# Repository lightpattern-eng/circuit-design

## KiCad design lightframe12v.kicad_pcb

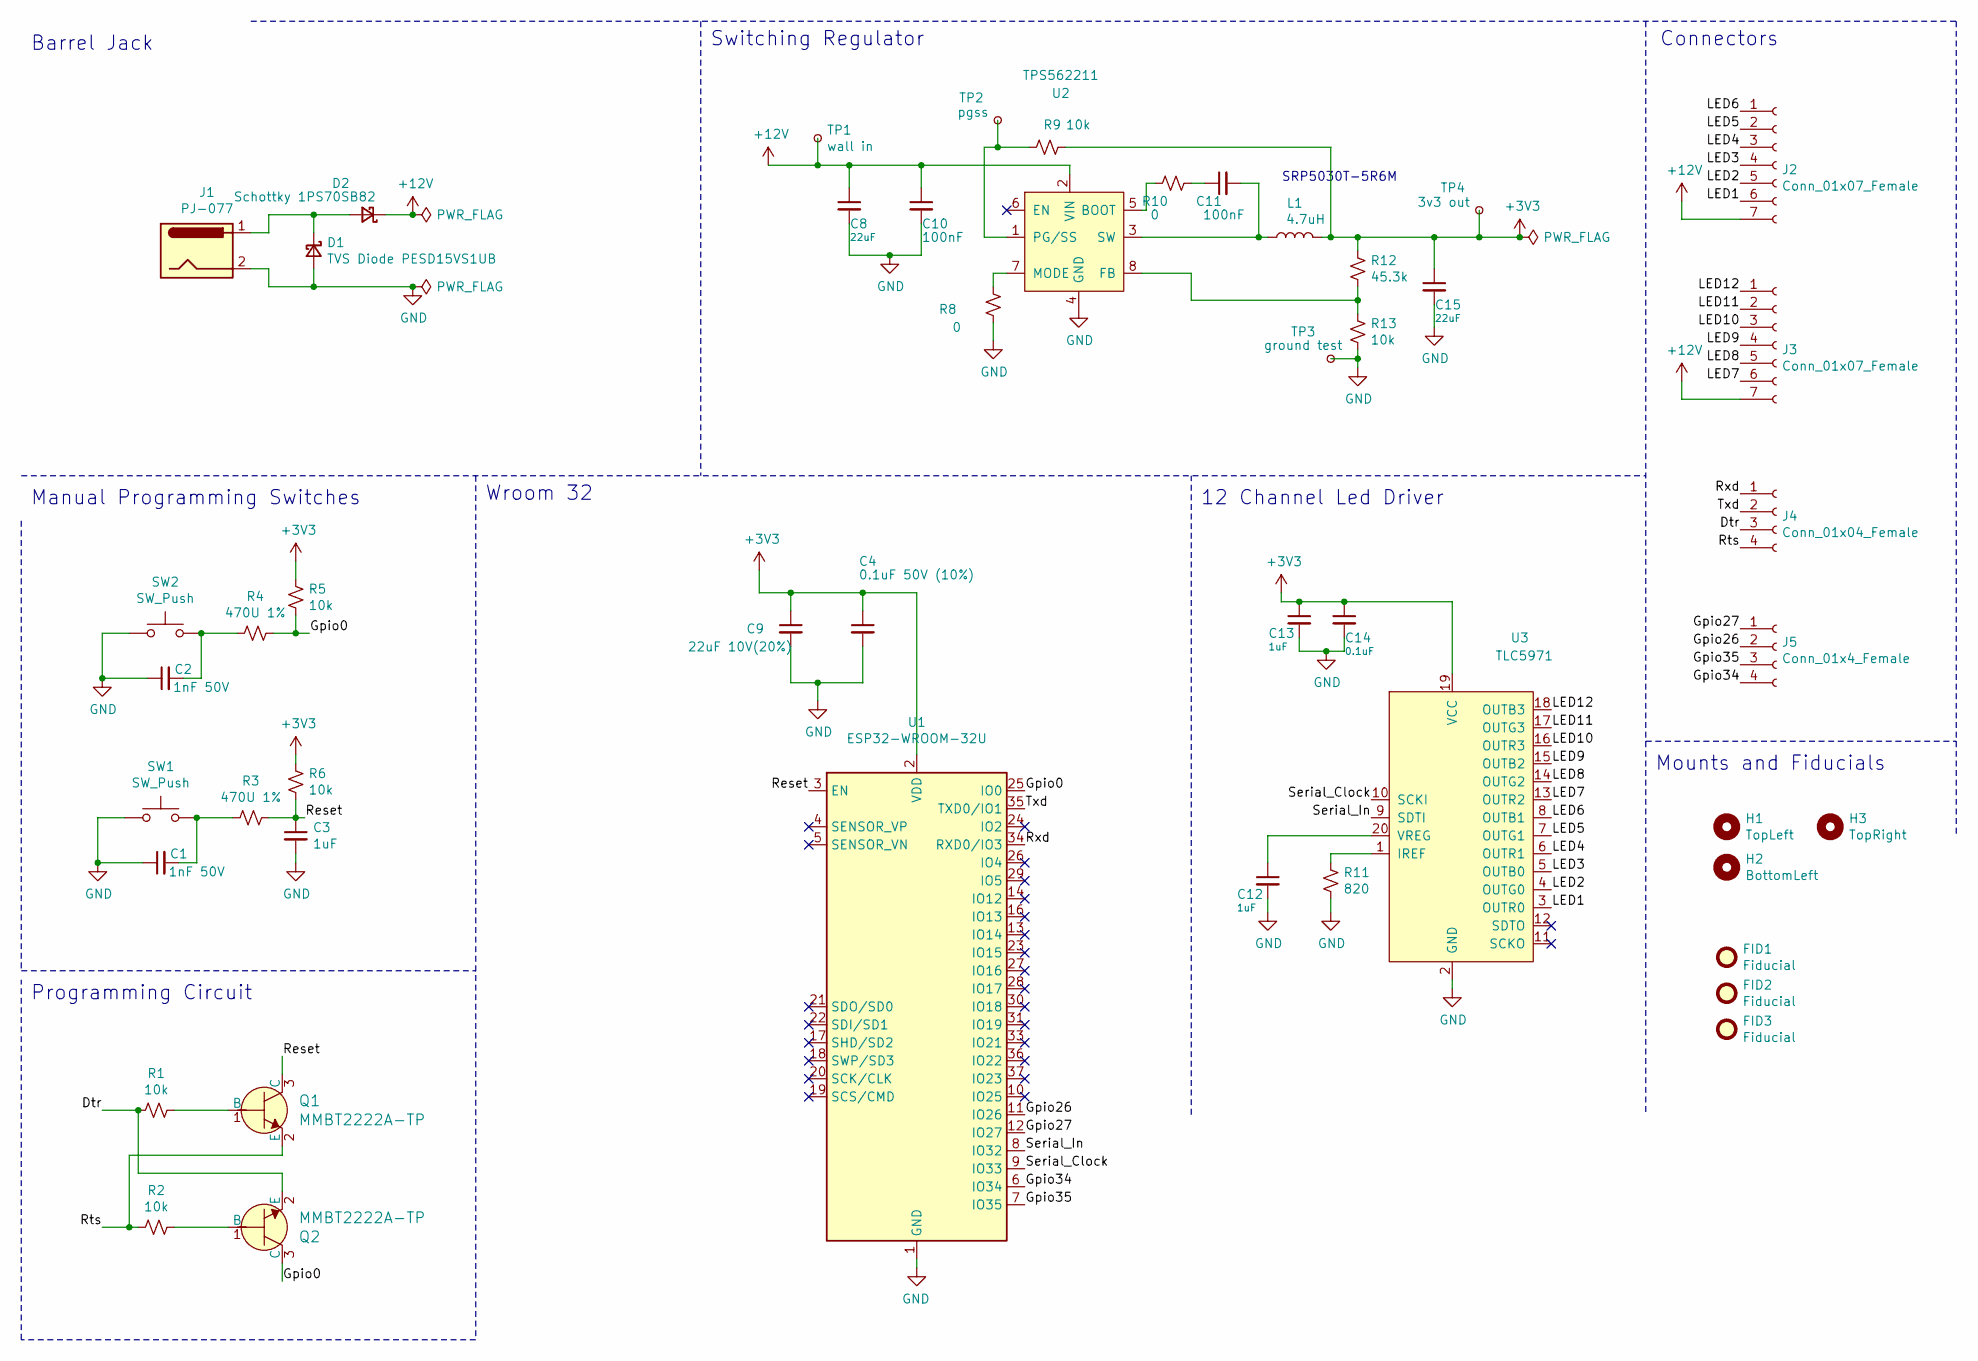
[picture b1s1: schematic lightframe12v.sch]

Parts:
C1, C2: 1nF 50V; 0603
C3, C12, C13: 1uF; 0603
C4: 0.1uF 50V (10%); 0603
C8: 22uF; 1206
C9: 22uF 10V(20%); 0805
C10: 100nF; 0603
C11: 100nF; 0805
C14: 0.1uF; 0603
C15: 22uF; 0805
D1: TVS Diode PESD15VS1UB; D_SOD-523
D2: Schottky 1PS70SB82; SOT-323
FID1, FID2, FID3: Fiducial; Fiducial_1mm_Mask2mm
H1: TopLeft; MountingHole_2.2mm_M2
H2: BottomLeft; MountingHole_2.2mm_M2
H3: TopRight; MountingHole_2.2mm_M2
J1: PJ-077; CUI_PJ-077
J2, J3: Conn_01x07_Female; PinHeader_1x07_P2.54mm_Vertical
J4: Conn_01x04_Female; PinSocket_1x04_P2.54mm_Vertical
J5: Conn_01x4_Female; PinHeader_1x04_P2.54mm_Vertical
L1: 4.7uH; SRP5030T-5R6M
Q1, Q2: MMBT2222A-TP; SOT-23-3; MPN MMBT2222A-TP; Digi-Key_PN MMBT2222ATPMSCT-ND
R1, R2, R5, R6: 10k; R_0402_1005Metric
R3, R4: 470U 1%; 0603
R8, R10: 0; 0603
R9, R13: 10k; 0603
R11: 820; 0603
R12: 45.3k; 0603
SW1, SW2: SW_Push; PTS810 Tactile Switch
TP1: wall in; TestPoint_Pad_1.5x1.5mm
TP2: pgss; TestPoint_Pad_1.5x1.5mm
TP3: ground test; TestPoint_Pad_1.5x1.5mm
TP4: 3v3 out; TestPoint_Pad_1.5x1.5mm
U1: ESP32-WROOM-32U
U2: TPS562211; TPS562211 12V pmic
U3: TLC5971; HTSSOP-20-1EP_4.4x6.5mm_P0.65mm_EP3.4x6.5mm_Mask2.75x3.43mm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

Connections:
+3V3: C4.1, C9.1, C13.1, C14.1, C15.1, L1.2, R5.1, R6.1, R9.1, R12.1, TP4.1, U1.2 (VDD), U3.19 (VCC)
+12V: C8.1, C10.1, D2.1 (K), J2.7, J3.7, TP1.1, U2.2 (VIN)
/Dtr: J4.3, Q2.2 (E), R1.2
/Gpio0: Q2.3 (C), R4.2, R5.2, U1.25 (IO0)
/Gpio26: J5.2, U1.11 (IO26)
/Gpio27: J5.1, U1.12 (IO27)
/Gpio34: J5.4, U1.6 (IO34)
/Gpio35: J5.3, U1.7 (IO35)
/LED1: J2.6, U3.3 (OUTR0)
/LED2: J2.5, U3.4 (OUTG0)
/LED3: J2.4, U3.5 (OUTB0)
/LED4: J2.3, U3.6 (OUTR1)
/LED5: J2.2, U3.7 (OUTG1)
/LED6: J2.1, U3.8 (OUTB1)
/LED7: J3.6, U3.13 (OUTR2)
/LED8: J3.5, U3.14 (OUTG2)
/LED9: J3.4, U3.15 (OUTB2)
/LED10: J3.3, U3.16 (OUTR3)
/LED11: J3.2, U3.17 (OUTG3)
/LED12: J3.1, U3.18 (OUTB3)
/Reset: C3.1, Q1.3 (C), R3.2, R6.2, U1.3 (EN)
/Rts: J4.4, Q1.2 (E), R2.2
/Rxd: J4.1, U1.34 (RXD0/IO3)
/Serial_Clock: U1.9 (IO33), U3.10 (SCKI)
/Serial_In: U1.8 (IO32), U3.9 (SDTI)
/Txd: J4.2, U1.35 (TXD0/IO1)
GND: C1.1, C2.1, C3.2, C4.2, C8.2, C9.2, C10.2, C12.2, C13.2, C14.2, C15.2, D1.2 (A), J1.2, R8.1, R11.2, R13.2, SW1.1, SW2.1, TP3.1, U1.1 (GND), U1.15 (GND), U1.38 (GND), U1.39 (GND), U2.4 (GND), U3.2 (GND)
unnamed: C1.2, R3.1, SW1.2
unnamed: C2.2, R4.1, SW2.2
unnamed: C11.1, R10.2
unnamed: C11.2, L1.1, U2.3 (SW)
unnamed: C12.1, U3.20 (VREG)
unnamed: D1.1 (K), D2.2 (A), J1.1
unnamed: Q1.1 (B), R1.1
unnamed: Q2.1 (B), R2.1
unnamed: R8.2, U2.7 (MODE)
unnamed: R9.2, TP2.1, U2.1 (PG/SS)
unnamed: R10.1, U2.5 (BOOT)
unnamed: R11.1, U3.1 (IREF)
unnamed: R12.2, R13.1, U2.8 (FB)

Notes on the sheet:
Mounts and Fiducials
Connectors
Switching Regulator
Barrel Jack
12 Channel Led Driver
Programming Circuit
Manual Programming Switches
Wroom 32
SRP5030T-5R6M

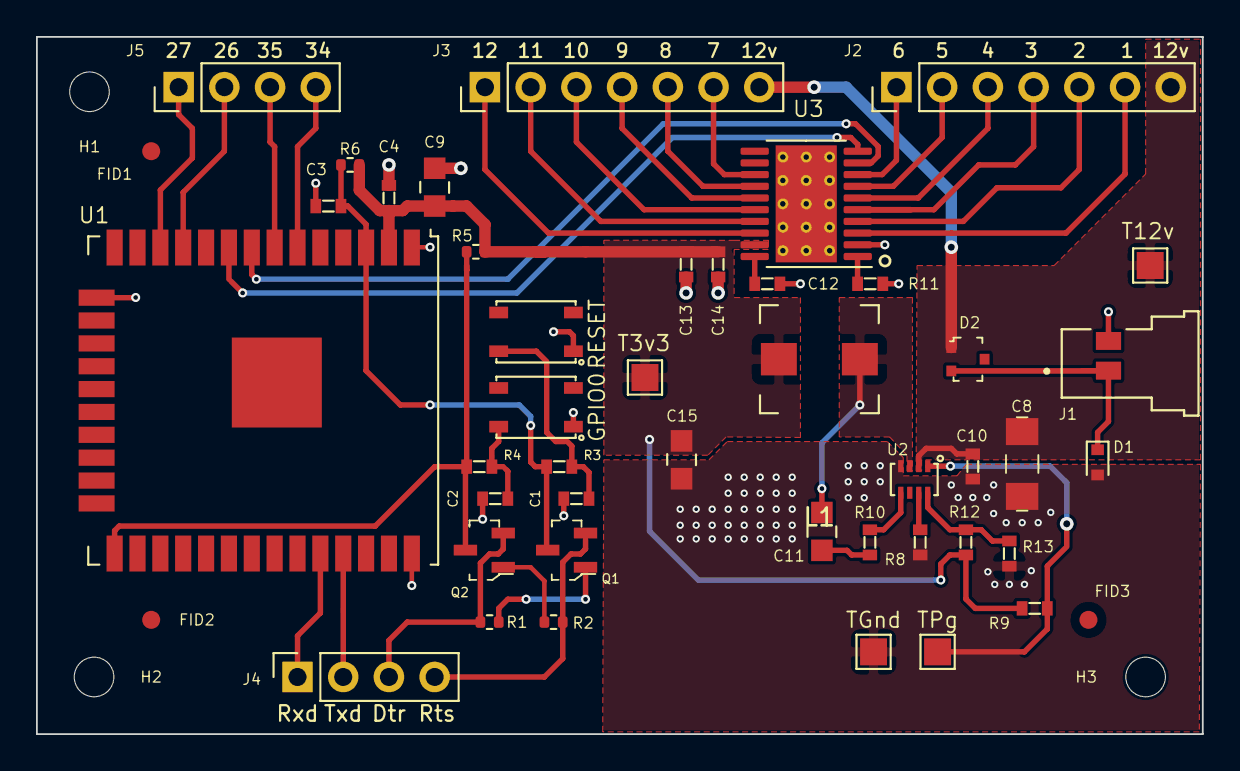
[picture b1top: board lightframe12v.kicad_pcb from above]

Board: 2 copper layers, 64.8 x 38.7 mm, 49 parts (0 on the bottom side), 40 nets.

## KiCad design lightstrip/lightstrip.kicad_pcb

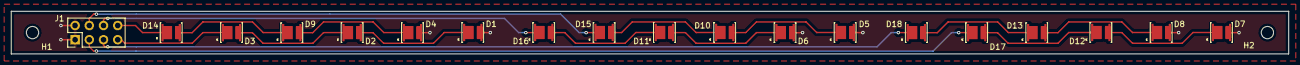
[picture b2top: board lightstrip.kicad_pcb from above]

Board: 2 copper layers, 228.6 x 7.6 mm, 21 parts (0 on the bottom side), 19 nets.

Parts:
D1: w1; SeoulSunlike3030
D2: w2; SeoulSunlike3030
D3: w3; SeoulSunlike3030
D4: c1; SeoulSunlike3030
D5: w4; SeoulSunlike3030
D6: c4; SeoulSunlike3030
D7: w7; SeoulSunlike3030
D8: c7; SeoulSunlike3030
D9: c2; SeoulSunlike3030
D10: w5; SeoulSunlike3030
D11: c5; SeoulSunlike3030
D12: w8; SeoulSunlike3030
D13: c8; SeoulSunlike3030
D14: c3; SeoulSunlike3030
D15: w6; SeoulSunlike3030
D16: c6; SeoulSunlike3030
D17: w9; SeoulSunlike3030
D18: c9; SeoulSunlike3030
H1, H2: MountingHole; MountingHole_2.2mm_M2
J1: Connector; PinHeader_2x04_P2.54mm_Vertical

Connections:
+12V: D1.2, D4.2, D5.2, D6.2, D7.2, D8.2, J1.1, J1.2
/cool1: D14.1, J1.8
/cool2: D16.1, J1.6
/cool3: D18.1, J1.5
/warm1: D3.1, J1.7
/warm2: D15.1, J1.4
/warm3: D17.1, J1.3
unnamed: D1.1, D2.2
unnamed: D2.1, D3.2
unnamed: D4.1, D9.2
unnamed: D10.1, D15.2
unnamed: D5.1, D10.2
unnamed: D11.1, D16.2
unnamed: D6.1, D11.2
unnamed: D12.1, D17.2
unnamed: D7.1, D12.2
unnamed: D13.1, D18.2
unnamed: D8.1, D13.2
unnamed: D9.1, D14.2

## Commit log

2021-03-04 adds 12v
2021-03-04 missing symbols
2021-03-06 Adds fiducials.
2021-03-07 Updates header footprints.
2021-03-07 changes footprint to TLC5971
2021-03-07 creates new symbol TLC5971
2021-03-09 initial layout of wroom
2021-03-09 improves wroom layout
2021-03-10 Rearranges around power traces.
2021-03-11 Moves led driver
2021-03-12 rotated pmic
2021-03-16 Created pmic footprint
2021-03-16 Changed schematic to powerbench design
2021-03-19 Adds new TPS56221 pmic
2021-03-20 Adds TPS56221 footprint
2021-03-20 Label position
2021-03-20 Adds TPS56221 footprint
    Label position
2021-03-21 Rough layout of pmic
2021-03-22 Pmic zones
2021-03-23 Top ground plane with cutouts.
2021-03-23 Top ground no cutouts.
2021-03-24 Pmic refactor.
2021-03-25 Strip layout.
2021-03-26 Spread strip to 9".
2021-03-29 More layout.
2021-04-01 Plane cleanup and power rails.
2021-04-02 Connecting reset and gpio0.
2021-04-04 More routing.
2021-04-05 Fixes DRC errors.
2021-04-05 Removes extra thermal pin.
2021-04-06 Fiducials and mount points.
2021-04-07 Spaced out.
2021-04-11 changes inductor footprint.
2021-04-11 Reduced decoupling and increased traces.
2021-04-14 Adds spacing.
